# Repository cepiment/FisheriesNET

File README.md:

# FisheriesNET
Low Cost Solar Powered GPS Trackers

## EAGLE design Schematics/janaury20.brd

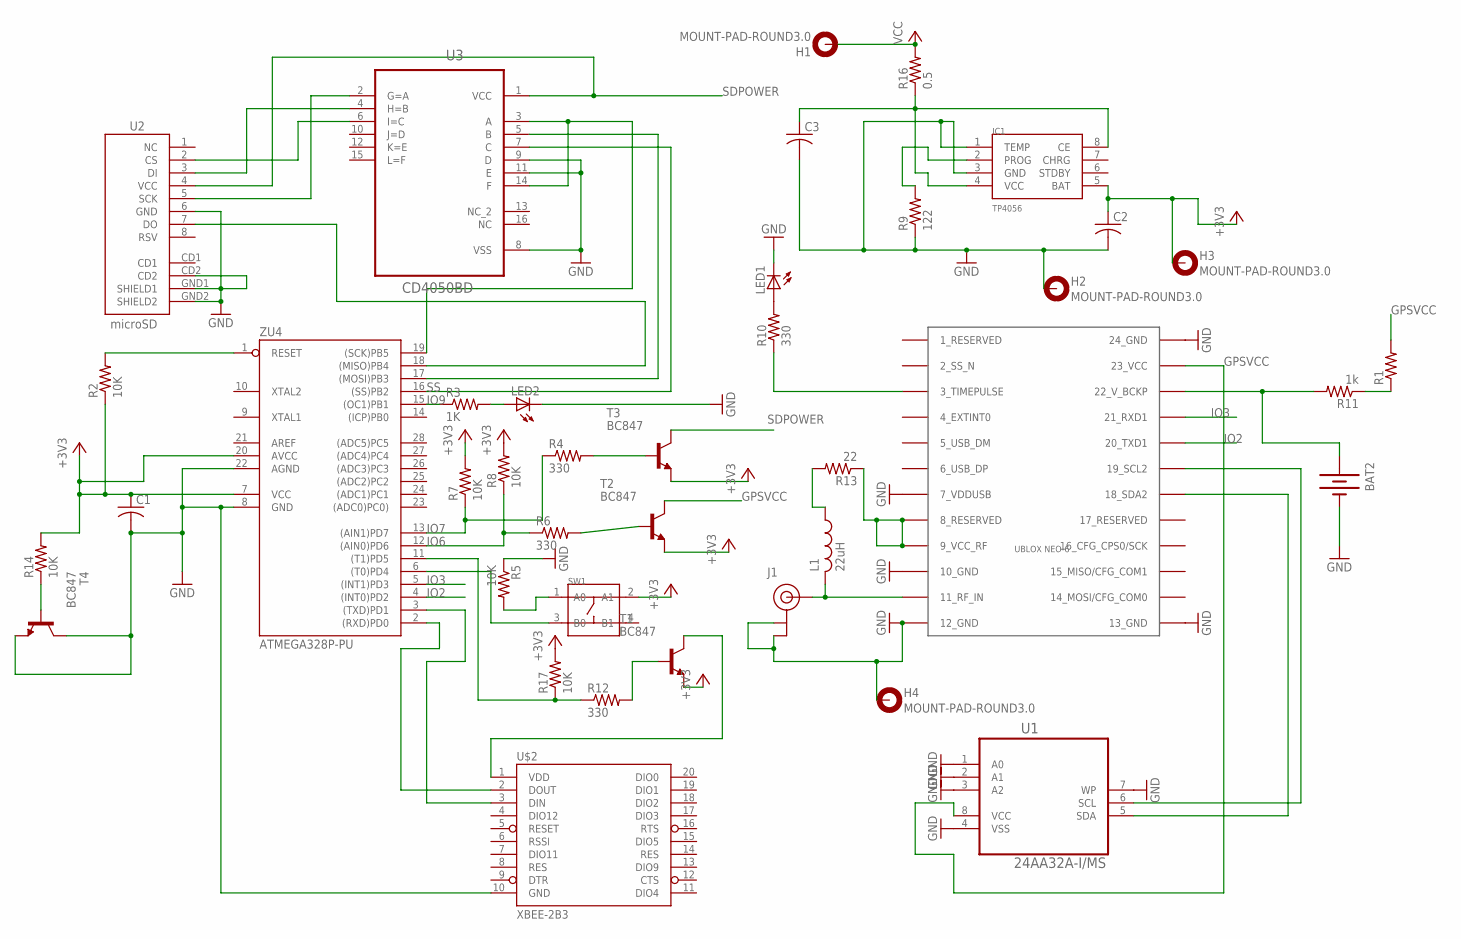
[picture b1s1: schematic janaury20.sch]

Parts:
BAT2: BATTERY12PTH; BATTCON_12MM_PTH
C1: C-USC1608; C1608
C2, C3: C-USC2012; C2012
H1, H2, H3, H4: MOUNT-PAD-ROUND3.0; 3,0-PAD
IC1: TP4056; SOP-8
J1: U.FL
L1: 22uH; L2012C
LED1, LED2: LEDSMT1206; 1206
R1: R-US_R0805; R0805
R2, R5, R7, R8, R14, R17: 10K; M3216
R3: 1K; M3216
R4, R6, R10, R12: 330; M3216
R9: 122; M3216
R11: 1k; M3216
R13: 22; M3216
R16: 0.5; M2012
SW1: SMD-BUTTON(4P-5.2X5.2X1.5MM-SKQGAKE010)-SKQGAKE010; SW4-SMD-5.2X5.2X1.5MM
T1, T2, T3, T4: BC847; SOT23
U1: 24AA32A-I/MS; SOP65P490X110-8N
U2: microSD; MICRO-SD-SOCKET-PP
U3: CD4050BD; SOIC127P600X175-16N
U$1: UBLOX_NEO-6; UBLOX_NEO-6P
U$2: XBEE-2B3; XBEE-SMD
ZU4: ATMEGA328P-PU; DIL28-3

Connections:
+3V3: C1.1, C2.1, H3.B3,0, IC1.5 (BAT), R2.1, R7.2, R8.2, R14.2, R17.2, SW1.2 (A1), T1.2 (E), T2.2 (E), T3.2 (E), ZU4.7 (VCC), ZU4.20 (AVCC)
CS: U2.2 (CS), U3.6 (I=C)
GND: BAT2.GND (-), C1.2, C2.2, C3.2, H2.B3,0, H4.B3,0, IC1.1 (TEMP), IC1.3 (GND), J1.P$1 (GND), J1.P$2 (GND), LED1.C, LED2.C, R5.1, R9.1, T4.2 (E), T4.3 (C), U1.1 (A0), U1.2 (A1), U1.3 (A2), U1.4 (VSS), U1.7 (WP), U2.6 (GND), U2.CD2, U2.GND1 (SHIELD1), U2.GND2 (SHIELD2), U3.8 (VSS), U3.9 (D), U3.11 (E), U$1.7_VDDUSB, U$1.10_GND, U$1.12_GND, U$1.13_GND, U$1.24_GND, U$2.10 (GND), ZU4.8 (GND), ZU4.22 (AGND)
GPSVCC: R1.2, T2.3 (C), U1.8 (VCC), U$1.23_VCC
IO2: U$1.20_TXD1, ZU4.4 ((INT0)PD2)
IO3: U$1.21_RXD1, ZU4.5 ((INT1)PD3)
IO6: R6.1, R8.1, ZU4.12 ((AIN0)PD6)
IO7: R4.1, R7.1, ZU4.13 ((AIN1)PD7)
IO9: R3.1, ZU4.15 ((OC1)PB1)
MOSI: U3.5 (B), ZU4.17 ((MOSI)PB3)
unnamed: U2.7 (DO), ZU4.18 ((MISO)PB4)
unnamed: LED2.A, R3.2
unnamed: LED1.A, R10.2
unnamed: R5.2, SW1.1 (A0)
unnamed: SW1.3 (B0), ZU4.6 ((T0)PD4)
unnamed: R4.2, T3.1 (B)
unnamed: R6.2, T2.1 (B)
unnamed: U1.6 (SCL), U$1.19_SCL2
unnamed: R12.1, R17.1, ZU4.11 ((T1)PD5)
unnamed: L1.1, R13.2
unnamed: U2.3 (DI), U3.4 (H=B)
unnamed: R12.2, T1.1 (B)
unnamed: R13.1, U$1.8_RESERVED, U$1.9_VCC_RF
unnamed: R14.1, T4.1 (B)
unnamed: J1.P$3 (SIGNAL), L1.2, U$1.11_RF_IN
unnamed: BAT2.VCC@1 (+), R11.2, U$1.22_V_BCKP
unnamed: U1.5 (SDA), U$1.18_SDA2
unnamed: R1.1, R11.1
unnamed: IC1.2 (PROG), R9.2
unnamed: U$2.2 (DOUT), ZU4.2 ((RXD)PD0)
unnamed: U$2.3 (DIN), ZU4.3 ((TXD)PD1)
unnamed: C3.1, IC1.4 (VCC), IC1.8 (CE), R16.1
unnamed: T1.3 (C), U$2.1 (VDD)
RESET: R2.2, ZU4.1 (RESET)
SCK: U3.3 (A), U3.14 (F), ZU4.19 ((SCK)PB5)
SCK1: U2.5 (SCK), U3.2 (G=A)
SCK2: R10.1, U$1.3_TIMEPULSE
SDPOWER: T3.3 (C), U2.4 (VCC), U3.1 (VCC)
SS: U3.7 (C), ZU4.16 ((SS)PB2)
VCC: H1.B3,0, R16.2

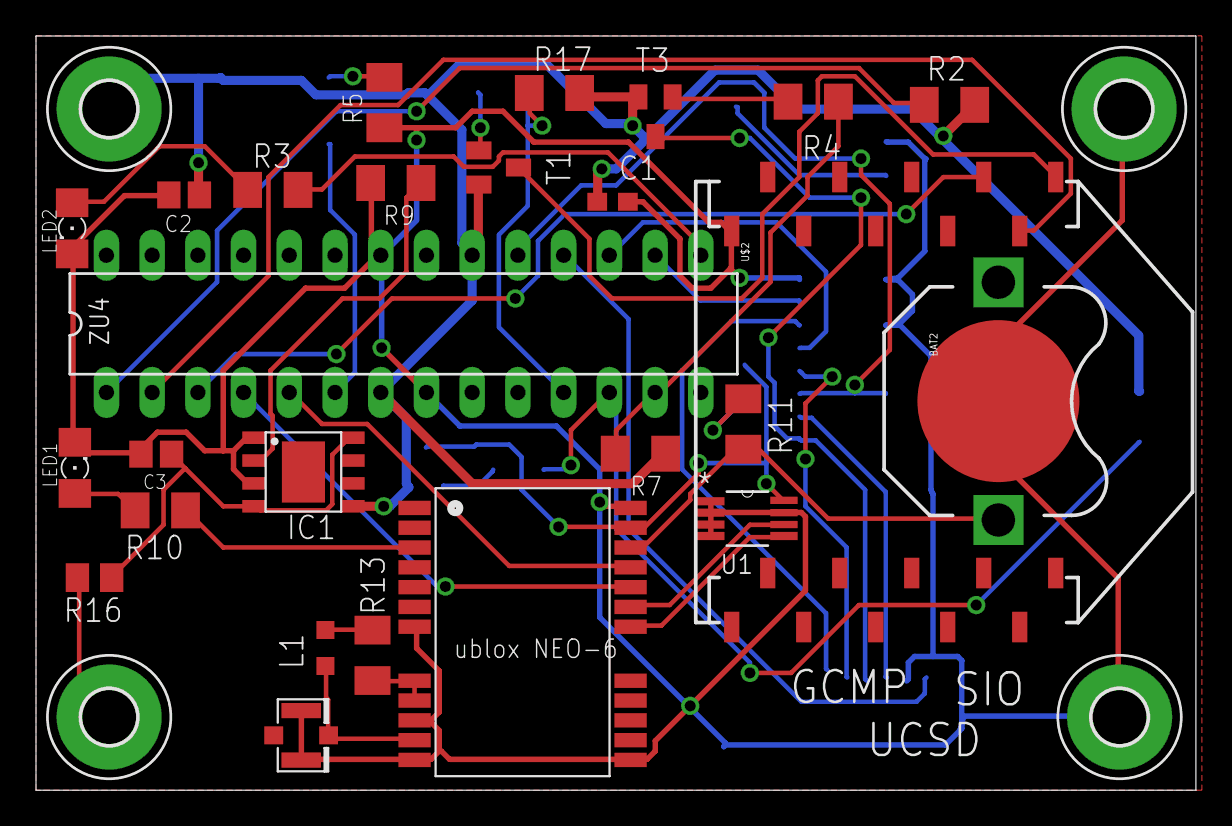
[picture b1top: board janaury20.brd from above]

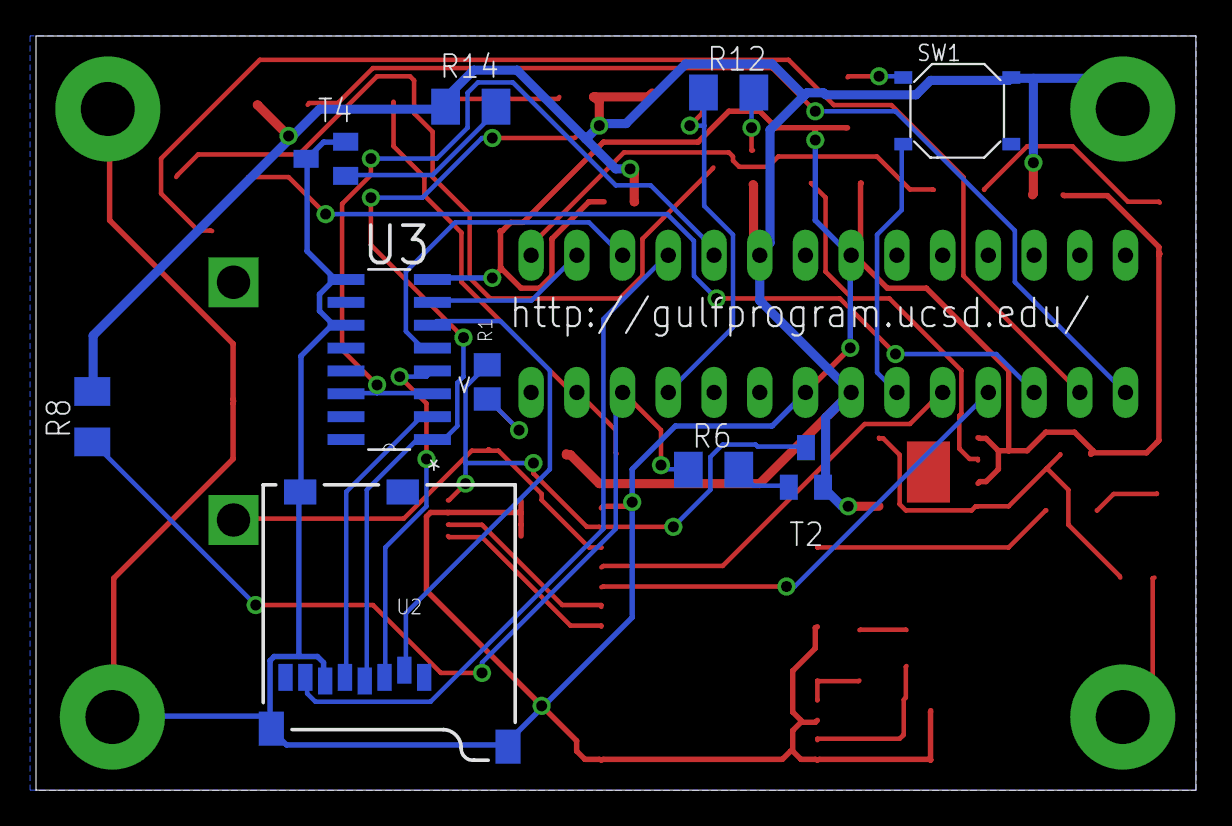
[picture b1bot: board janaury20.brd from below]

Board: 2 copper layers, 64.4 x 41.9 mm, 40 parts (10 on the bottom side), 40 nets.

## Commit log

2016-08-29 Create Micro-controller Code
2016-08-29 Create blank
2016-08-29 Update and rename blank to Settings
2016-08-29 Update Settings
2016-08-30 Rename Readme to README

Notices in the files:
parts and their libraries:
SparkFun-Electromechanical: Licensing: Creative Commons ShareAlike 4.0 International - https://creativecommons.org/licenses/by-sa/4.0
